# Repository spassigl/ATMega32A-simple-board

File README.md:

# ATMega32A demo board
An ATMega32A demo board with exposed GPIO pins, LEDs, tactile switches and a buzzer

## The project
This is a simple ATMega32A board that I used to test some ideas for a bigger project. 
It's a small factor pcb - 84x44mm - with the following features:
- ATMega32A clocked at 16MHz
- USB-C conneector for power and, with a booloader like urboot, for firmware updates and serial communication. 
- ISP 6-pin connector to flash bootloader or firmware (in case you don't want to use a booloader like urboot or optiboot)
- Power OR-ing - can have both ISP and USB connected
- All the unused GPIO pins are exposed via connectors on the side of the board
- Includes a buzzer, two LEDs, two tactile buttons
- Footprints are optimized for JLCPCB and "Basic" or "Preferred Extended" parts, to lower assembly costs

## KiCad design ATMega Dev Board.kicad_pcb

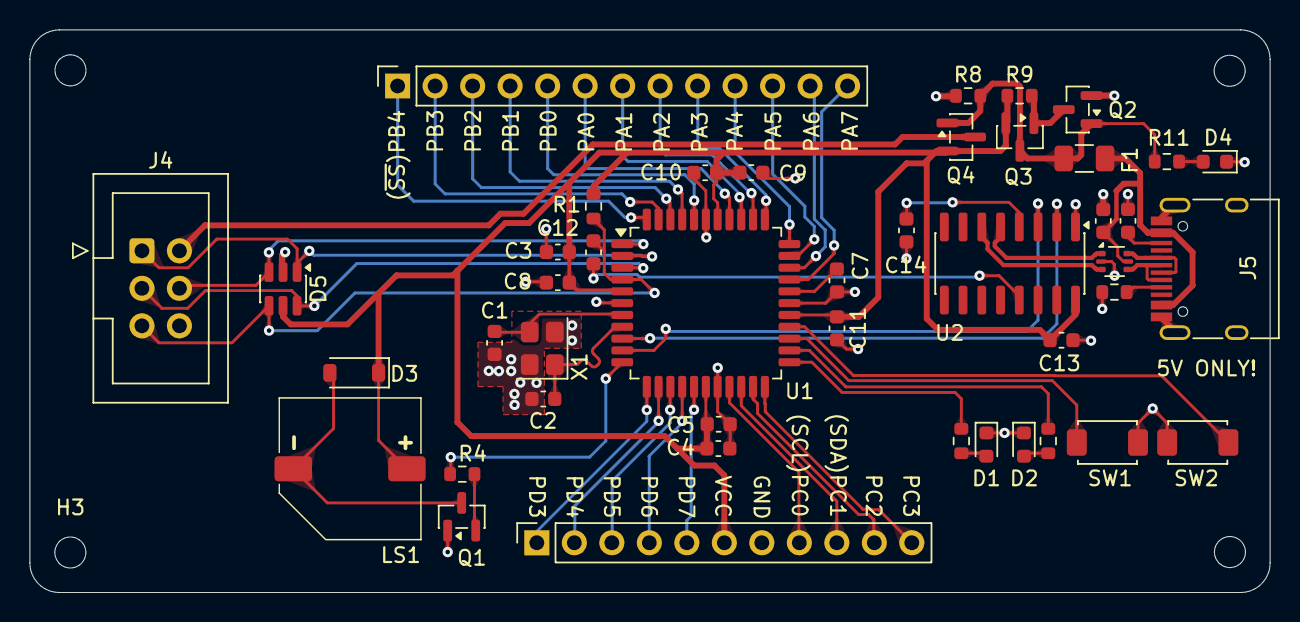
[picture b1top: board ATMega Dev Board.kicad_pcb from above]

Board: 4 copper layers, 84.0 x 38.1 mm, 48 parts (0 on the bottom side), 55 nets.

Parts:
C1, C2: 22p; C_0603_1608Metric
C3, C4, C9: 4.7u; C_0603_1608Metric
C5, C6, C7, C8, C10, C11, C12, C13, C14: 0.1u; C_0603_1608Metric
D1, D2, D4: LED; LED_0603_1608Metric
D3: 1N4001; D_SOD-123
D5: SRV05; SOT-23-6
F1: 1A; Fuse_1206_3216Metric
H1, H2, H3, H4: MountingHole; MountingHole_2.1mm
J1: Conn_01x13; PinSocket_1x13_P2.54mm_Vertical
J2: Conn_01x09; PinSocket_1x11_P2.54mm_Vertical
J4: SPI header; IDC-Header_2x03_P2.54mm_Vertical
J5: USB-C_31-M-12; USB_C_Receptacle_HRO_TYPE-C-31-M-12
LS1: Speaker; Buzzer_MLT-9650
Q1: S8050; SOT-23
Q2: 2N7002; SOT-23
Q3, Q4: HL6042; SOT-23
R1: 10k; R_0603_1608Metric
R2, R3: 220; R_0603_1608Metric
R4: 1k; R_0603_1608Metric
R5: 5k1; R_0603_1608Metric
R6: 5k1; C_0603_1608Metric
R8, R9: 330k; R_0603_1608Metric
R11: 510; R_0603_1608Metric
SW1, SW2: SW_SPST; Switch_TS-1088-AR02016
U1: ATmega32A-A; TQFP-44_10x10mm_P0.8mm
U2: CH340C; SOIC-16_3.9x9.9mm_P1.27mm
U3: USBLC6-2P6; SOT-666
X1: 16MHz; Crystal_SMD_3225-4Pin_3.2x2.5mm

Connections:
/LED1: R2.1, U1.23 ((TDO)PC4)
/LED2: R3.1, U1.24 ((TDI)PC5)
/MISO: D5.1 (IO1), J4.1 (MISO), U1.2 ((MISO)PB6)
/MOSI: D5.3 (IO2), J4.4 (MOSI), U1.1 ((MOSI)PB5)
/PA0: J1.6, U1.37 ((ADC0)PA0)
/PA1: J1.7, U1.36 ((ADC1)PA1)
/PA2: J1.8, U1.35 ((ADC2)PA2)
/PA3: J1.9, U1.34 ((ADC3)PA3)
/PA4: J1.10, U1.33 ((ADC4)PA4)
/PA5: J1.11, U1.32 ((ADC5)PA5)
/PA6: J1.12, U1.31 ((ADC6)PA6)
/PA7: J1.13, U1.30 ((ADC7)PA7)
/PB0: J1.5, U1.40 ((XCK/T0)PB0)
/PB1: J1.4, U1.41 ((T1)PB1)
/PB2: J1.3, U1.42 ((AIN0/INT2)PB2)
/PB3: J1.2, U1.43 ((AIN1/OC0)PB3)
/PB4: J1.1, U1.44 ((~SS)PB4)
/PC0: J2.8, U1.19 ((SCL)PC0)
/PC1: J2.9, U1.20 ((SDA)PC1)
/PC2: J2.10, U1.21 ((TCK)PC2)
/PC3: J2.11, U1.22 ((TMS)PC3)
/PD3: J2.1, U1.12 ((INT1)PD3)
/PD4: J2.2, U1.13 ((OC1B)PD4)
/PD5: J2.3, U1.14 ((OC1A)PD5)
/PD6: J2.4, U1.15 ((ICP1)PD6)
/PD7: J2.5, U1.16 ((OC2)PD7)
/RST: C12.1, D5.4 (IO3), J4.5 (~RST), R1.2, U1.4 (~RESET)
/SCK: D5.6 (IO4), J4.3 (SCK), U1.3 ((SCK)PB7)
/SPKR: R4.1, U1.11 ((INT0)PD2)
/SW1: SW1.1 (A), U1.25 ((TOSC1)PC6)
/SW2: SW2.1 (A), U1.26 ((TOSC2)PC7)
/UD+: U2.5 (UD+), U3.1 (I/O1)
/UD-: U2.6 (UD-), U3.3 (I/O2)
/UD_N: J5.A7 (D-), J5.B7 (D-), U3.4 (I/O2)
/UD_P: J5.A6 (D+), J5.B6 (D+), U3.6 (I/O1)
/URXD: U1.10 ((TXD)PD1), U2.3 (RXD)
/UTXD: U1.9 ((RXD)PD0), U2.2 (TXD)
GND: C1.2, C2.2, C3.1, C4.1, C5.2, C6.2, C7.1, C8.2, C9.1, C10.2, C11.2, C13.1, C14.1, D1.1 (K), D2.1 (K), D4.1 (K), D5.2 (VN), J2.7, J4.6 (GND), J5.A1 (GND), J5.A12 (GND), J5.B1 (GND), J5.B12 (GND), J5.S1 (SHIELD), Q1.1 (E), Q2.2 (S), R5.1, R6.1, R8.1, SW1.2 (B), SW2.2 (B), U1.6 (GND), U1.18 (GND), U1.28 (GND), U1.39 (GND), U2.1 (GND), U3.2 (GND), X1.2 (G), X1.4 (G)
unnamed: D1.2 (A), R2.2
unnamed: D2.2 (A), R3.2
unnamed: D3.2 (A), LS1.2, Q1.3 (C)
unnamed: D4.2 (A), R11.2
unnamed: J5.A5 (CC1), R5.2
unnamed: J5.B5 (CC2), R6.2
unnamed: Q1.2 (B), R4.2
unnamed: Q2.3 (D), Q3.1 (G), R9.2
unnamed: C7.2, U1.29 (AREF)
unnamed: C2.1, U1.8 (XTAL1), X1.1
unnamed: C1.1, U1.7 (XTAL2), X1.3
unnamed: C14.2, U2.4 (V3)
unnamed: C12.2, U2.13 (~DTR)
VBUS: C6.1, F1.2, J5.A4 (VBUS), J5.A9 (VBUS), J5.B4 (VBUS), J5.B9 (VBUS), U3.5 (VBUS)
VCC: C3.2, C4.2, C5.1, C8.1, C9.2, C10.1, C11.1, C13.2, D3.1 (K), D5.5 (VP), J2.6, LS1.1, Q3.2 (S), Q4.2 (S), R1.1, R9.1, U1.5 (VCC), U1.17 (VCC), U1.27 (AVCC), U1.38 (VCC), U2.16 (VCC)
VSPI: J4.2 (VCC), Q4.3 (D)
VUSB: F1.1, Q2.1 (G), Q3.3 (D), Q4.1 (G), R8.2, R11.1

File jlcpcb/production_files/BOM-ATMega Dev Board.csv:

Comment,Designator,Footprint,LCSC,Quantity
0.1u,"C10,C11,C12,C13,C14,C5,C7,C8",C_0603_1608Metric,C14663,8
10k,R1,R_0603_1608Metric,C25804,1
16MHz,X1,Crystal_SMD_3225-4Pin_3.2x2.5mm,C13738,1
1N4001,D3,D_SOD-123,C7462829,1
1k,R4,R_0603_1608Metric,C21190,1
1u,C15,C_0603_1608Metric,C15849,1
220,"R11,R2,R3",R_0603_1608Metric,C22962,3
22p,"C1,C2",C_0603_1608Metric,C1653,2
2N7002,Q2,SOT-23,C8545,1
330k,"R8,R9",R_0603_1608Metric,C23137,2
4.7u,"C3,C4,C9",C_0603_1608Metric,C19666,3
500mA/24V,F1,Fuse_1206_3216Metric,C70077,1
5k1,"R5,R6",R_0402_1005Metric,C25905,2
ATmega32A-A,U1,TQFP-44_10x10mm_P0.8mm,C5659,1
CH340C,U2,SOIC-16_3.9x9.9mm_P1.27mm,C84681,1
HL6042,"Q3,Q4",Q_SOT-23,C28646264,2
LED,"D1,D2,D4",LED_0603_1608Metric,C2286,3
S8050,Q1,SOT-23,C2146,1
SPI header,J4,IDC-Header_2x03_P2.54mm_Vertical,C492441,1
SRV05,D5,SOT-23-6,C85364,1
SW_SPST,"SW1,SW2",Switch_TS-1088-AR02016,C720477,2
Speaker,LS1,Buzzer_MLT-9650,C96127,1
USB-C_31-M-12,J5,USB_C_Receptacle_HRO_TYPE-C-31-M-12,C165948,1
USBLC6-2P6,U3,SOT-666,C15999,1

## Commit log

2026-03-04 Version A
2026-03-04 added image
2026-03-04 Better traces
2026-03-06 Added power OR-ing
2026-03-07 Updated fabrication files
2026-03-08 corrected usb connections
2026-03-10 added USB ESD protection
2026-03-11 reviewed constraints
2026-03-11 correct UART signalling
2026-03-11 tweaked clearances
2026-03-12 update description
2026-03-12 added KiCad logo
2026-03-13 new stackup
2026-03-13 added teardrops
2026-03-14 updated constraints and traces
